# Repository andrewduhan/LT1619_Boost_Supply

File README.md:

LT1619_Boost_Supply
===================

Adjustable DC-DC boostmode power supply using the LT1619

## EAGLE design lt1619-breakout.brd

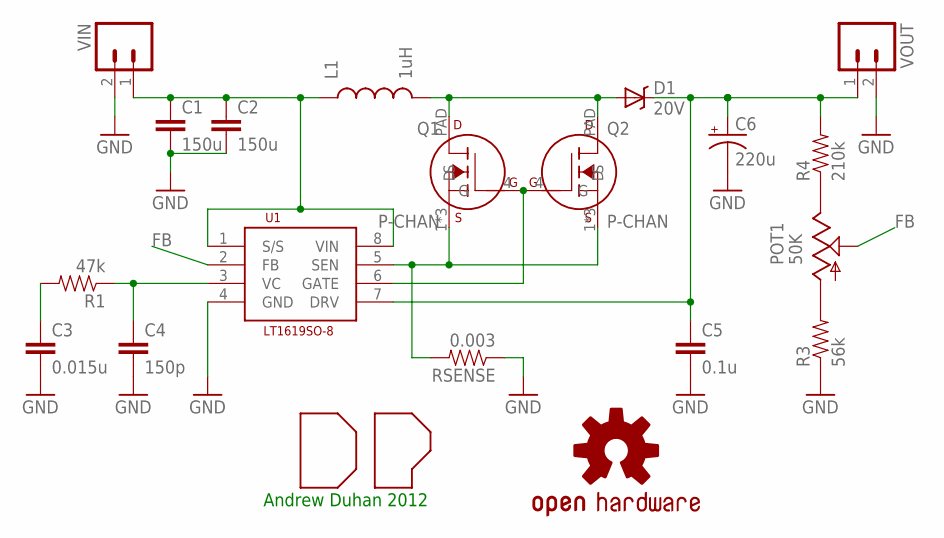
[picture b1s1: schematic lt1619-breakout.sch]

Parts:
C1, C2: 150u; 1210
C3: 0.015u; 0603-CAP
C4: 150p; 0603-CAP
C5: 0.1u; 0603-CAP
C6: 220u; EIA7343
D1: 20V; DO-214AB
L1: 1uH; INDUCTOR_10.9X10.0
POT1: 50K; POT-TOP-BOURNS
Q1, Q2: P-CHAN; LFPAK
R1: 47k; 0603-RES
R3: 56k; 0603-RES
R4: 210k; 0603-RES
RSENSE: 0.003; 1206
U1: LT1619SO-8; SOIC-08
U$2: DP_LOGO
U$4: OSHW-LOGOM; OSHW-LOGO-M
VIN: M02PTH; 1X02
VOUT: M02PTH; 1X02

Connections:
DRAIN: D1.A, L1.P$2 (2), Q1.PAD (D), Q2.PAD (D)
FB: POT1.2 (W), U1.2 (FB)
GATE: Q1.4 (G), Q2.4 (G), U1.6 (GATE)
GND: C1.2, C2.2, C3.2, C4.2, C5.2, C6.C (-), R3.1, RSENSE.1, U1.4 (GND), VIN.2, VOUT.2
unnamed: C3.1, R1.2
unnamed: POT1.3 (B), R4.1
unnamed: C4.1, R1.1, U1.3 (VC)
unnamed: POT1.1 (A), R3.2
SOURCE: Q1.1 (S), Q1.2 (S), Q1.3 (S), Q2.1 (S), Q2.2 (S), Q2.3 (S), RSENSE.2, U1.5 (SEN)
VBATT: C1.1, C2.1, L1.P$1 (1), U1.1 (S/S), U1.8 (VIN), VIN.1
VOUT: C5.1, C6.A (+), D1.C, R4.2, U1.7 (DRV), VOUT.1

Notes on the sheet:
Andrew Duhan 2012

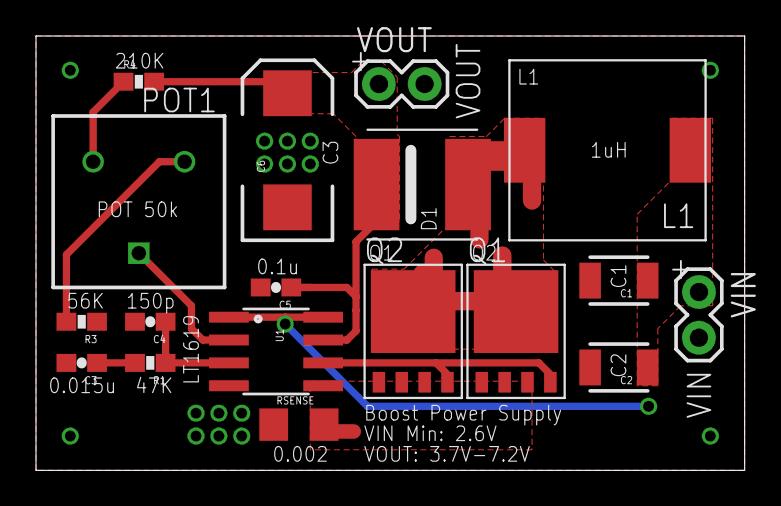
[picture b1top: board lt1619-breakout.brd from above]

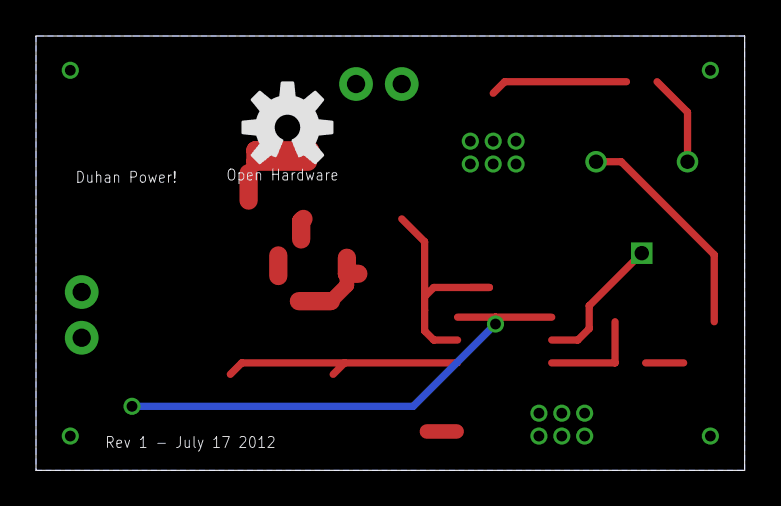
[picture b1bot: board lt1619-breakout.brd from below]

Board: 2 copper layers, 39.4 x 24.1 mm, 20 parts (2 on the bottom side), 11 nets.

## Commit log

2012-10-09 initial content
2012-10-09 schematic cleanup

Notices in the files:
parts and their libraries:
SparkFun-Passives: Licensing: CC v3.0 Share-Alike You are welcome to use this library for commercial purposes.
